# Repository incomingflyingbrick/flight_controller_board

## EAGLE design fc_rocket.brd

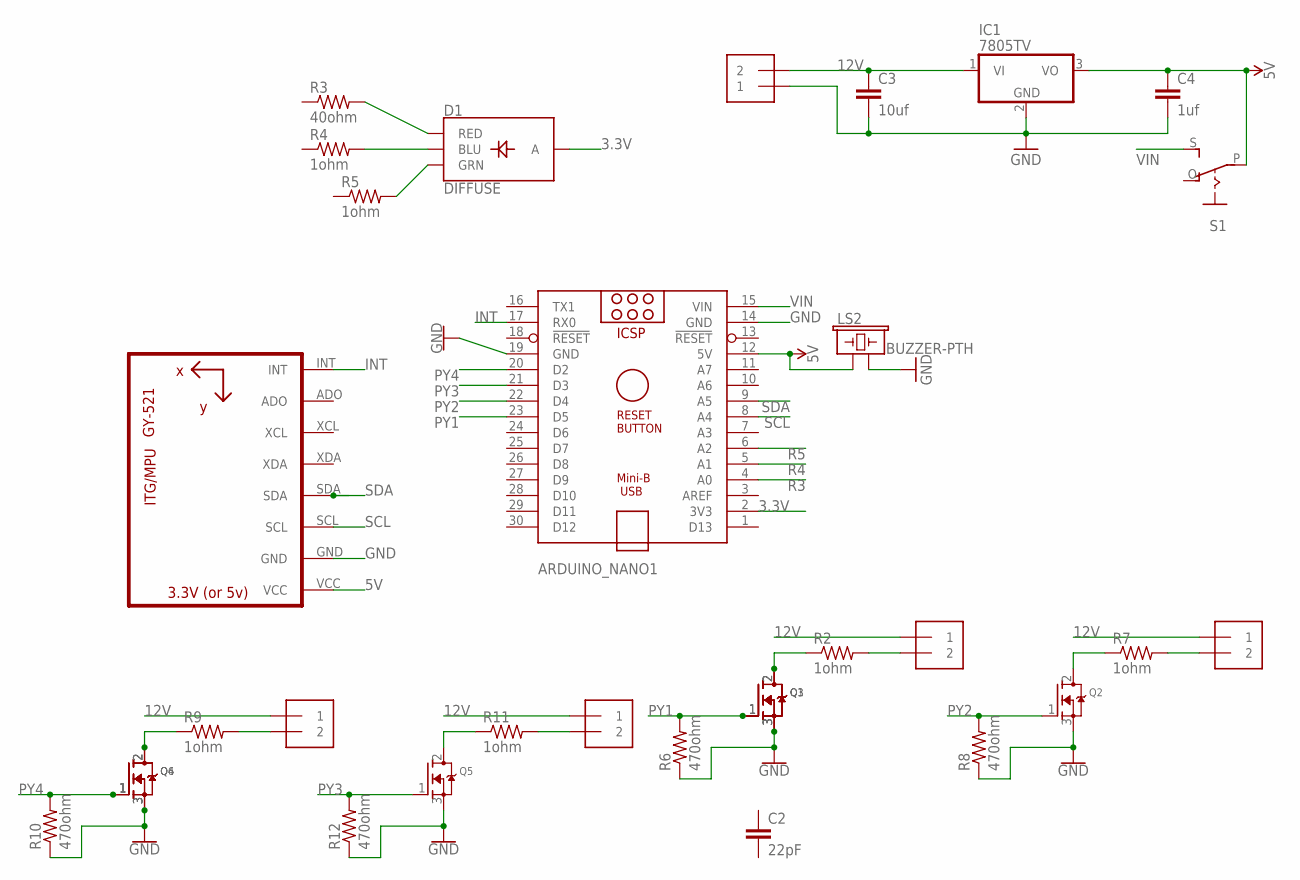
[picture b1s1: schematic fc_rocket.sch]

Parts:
ARDUINO_NANO1: ARDUINO_NANO
C2: 22pF; CAP-PTH-2.54
C3: 10uf; CAP-PTH-2.54
C4: 1uf; CAP-PTH-2.54
D1: DIFFUSE; LED-RGB-THRU
IC1: 7805TV; TO220V
J2, J3, J4, J5, J6: 1X2-3.5MM
LS2: BUZZER-PTH; BUZZER-12MM
Q1, Q2, Q3, Q4, Q5, Q6: MOSFET-NGDS_TO220V; TO220V
R2, R4, R5, R7, R9, R11: 1ohm; 0805-THM
R3: 40ohm; 0805-THM
R6, R8, R10, R12: 470ohm; 0805-THM
S1: EG1218S; EG1218
U2: GY-521MPU6050; GY-521

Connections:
3.3V: ARDUINO_NANO1.2 (3V3), D1.2 (A)
5V: ARDUINO_NANO1.12 (5V), C4.1, IC1.3 (VO), LS2.+ (1), S1.P, U2.VCC
12V: C3.1, IC1.1 (VI), J2.2, J3.1, J4.1, J5.1, J6.1
GND: ARDUINO_NANO1.14 (GND), ARDUINO_NANO1.19 (GND), C3.2, C4.2, IC1.2 (GND), J2.1, LS2.- (2), Q1.3 (S), Q2.3 (S), Q3.3 (S), Q4.3 (S), Q5.3 (S), Q6.3 (S), R6.1, R8.1, R10.1, R12.1, U2.GND
INT: ARDUINO_NANO1.17 (RX0), U2.INT
unnamed: D1.1 (RED), R3.2
unnamed: D1.4 (BLU), R4.2
unnamed: D1.3 (GRN), R5.2
unnamed: J3.2, R2.2
unnamed: Q1.2 (D), Q3.2 (D), R2.1
unnamed: J4.2, R7.2
unnamed: Q2.2 (D), R7.1
unnamed: J5.2, R9.2
unnamed: Q4.2 (D), Q6.2 (D), R9.1
unnamed: J6.2, R11.2
unnamed: Q5.2 (D), R11.1
PY1: ARDUINO_NANO1.23 (D5), Q1.1 (G), Q3.1 (G), R6.2
PY2: ARDUINO_NANO1.22 (D4), Q2.1 (G), R8.2
PY3: ARDUINO_NANO1.21 (D3), Q5.1 (G), R12.2
PY4: ARDUINO_NANO1.20 (D2), Q4.1 (G), Q6.1 (G), R10.2
R3: ARDUINO_NANO1.4 (A0)
R4: ARDUINO_NANO1.5 (A1)
R5: ARDUINO_NANO1.6 (A2)
SCL: ARDUINO_NANO1.8 (A4), U2.SCL
SDA: ARDUINO_NANO1.9 (A5), U2.SDA
VIN: ARDUINO_NANO1.15 (VIN), S1.S

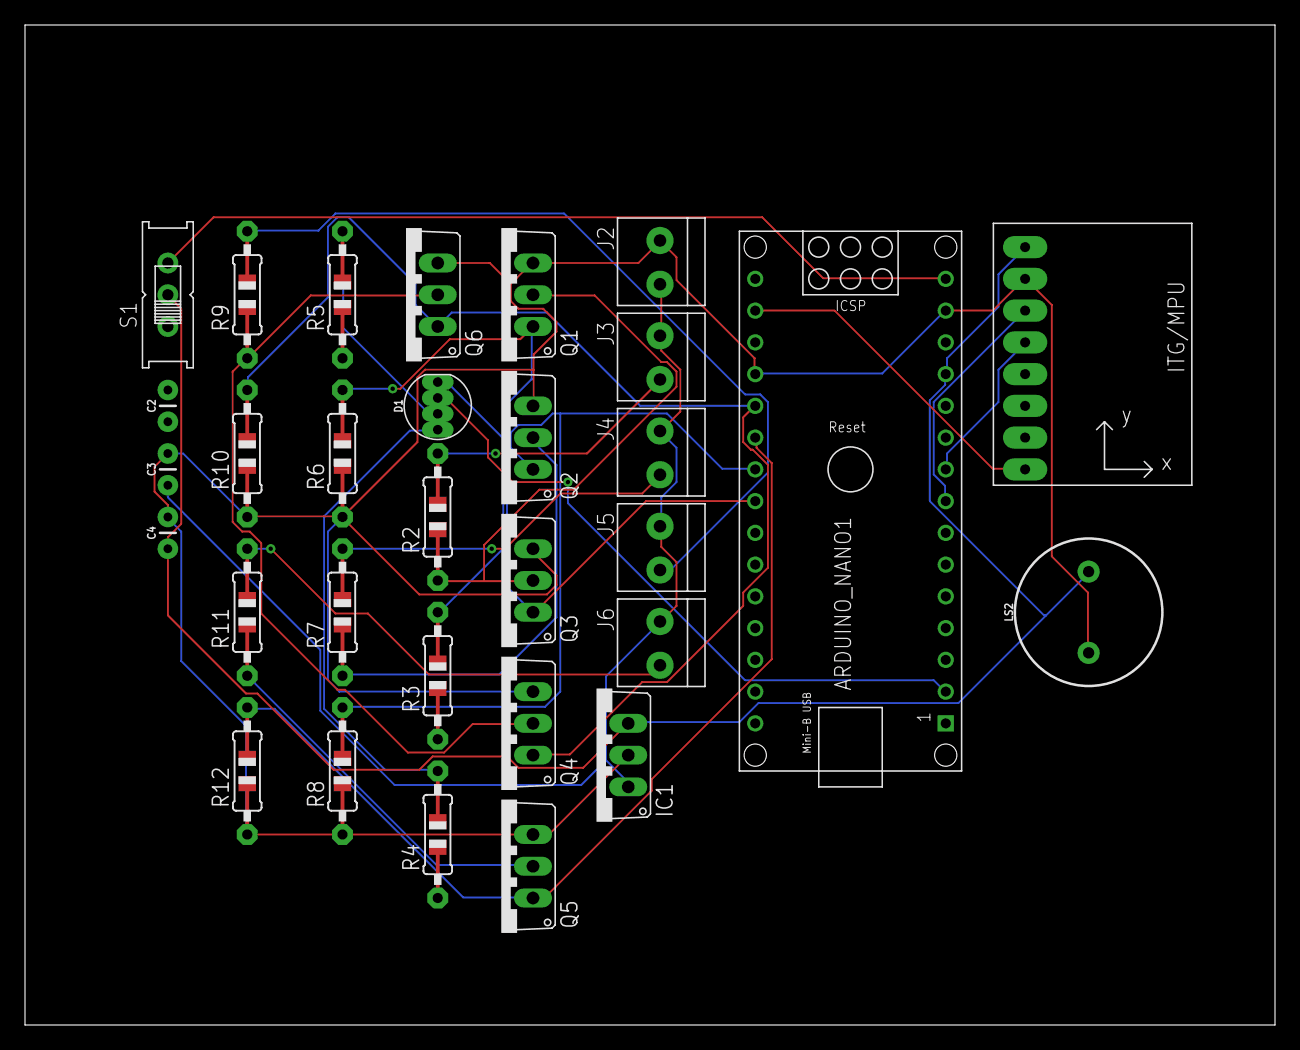
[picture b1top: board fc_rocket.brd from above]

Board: 2 copper layers, 100.0 x 80.0 mm, 31 parts (0 on the bottom side), 23 nets.

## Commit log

2019-01-19 first design
2019-01-19 finised auto router
2019-02-11 backup

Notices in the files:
parts and their libraries:
SparkFun-Capacitors: Licensing: Creative Commons ShareAlike 4.0 International - https://creativecommons.org/licenses/by-sa/4.0
